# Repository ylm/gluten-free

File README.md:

# Gluten-Free Project

## What is the Gluten-Free Project?

Gluten-Free Project is an open-source platform aimed at makers and musicians for real-time audio synthesis in a live setup.

It is meant to be portable, battery powered, small form factor self-contained and highly reconfigurable synthesizer.

GF-MINUS1 is the first iteration of the core of Gluten-Free. It features a low-power FPGA as its fully customizable soundchip and a SAME53 for high-speed communication. The soundchip provides two independant stereo outputs as well as a PMOD expansion interface. It is a bare-bone version designed to interface with expansion boards.

## Why Gluten-Free?

Gluten-Free was initiated to push the boundaries of what was available to makers with a music inclination.

It is also a platform meant to learn about digital design on a platform including an FPGA connected through an high-speed interface to a microcontroller.

## What can I do with Gluten-Free?

### GF-MINUS1

GF-MINUS1 is still in active development. As development progresses, the list of its capabilities is going to be expanded.

## Where is Gluten-Free Project going?

Gluten-Free is looking to expend the DIY synthesizer community and its userbase. The goal is to provide a powerful platform able to provide the computing power required for modern synthesizers for makers to focus on their desired implementation.

## How to get involved?

We are most on our [Discord channel](https://discord.gg/bngMxeF9Fw), so feel free to join and ask questions, offer suggestions, etc. The development is mostly done live on [gatin00b's Twitch channel](www.twitch.tv/gatin00b) is also a great place for discussion.

## Who's working on Gluten-Free?

* [@gatin00b](www.twitter.com/gatin00b) started the initial design. 
* [@overtinkerer]() provided help with documentation and support of the Gluten-Free platform.
* [@vmttmv]() provided guidance on microcontroller selection.
* [@BlindVia](https://www.twitch.tv/BlindVia) provided guidance for manufacturing and a full review of Gluten-Free

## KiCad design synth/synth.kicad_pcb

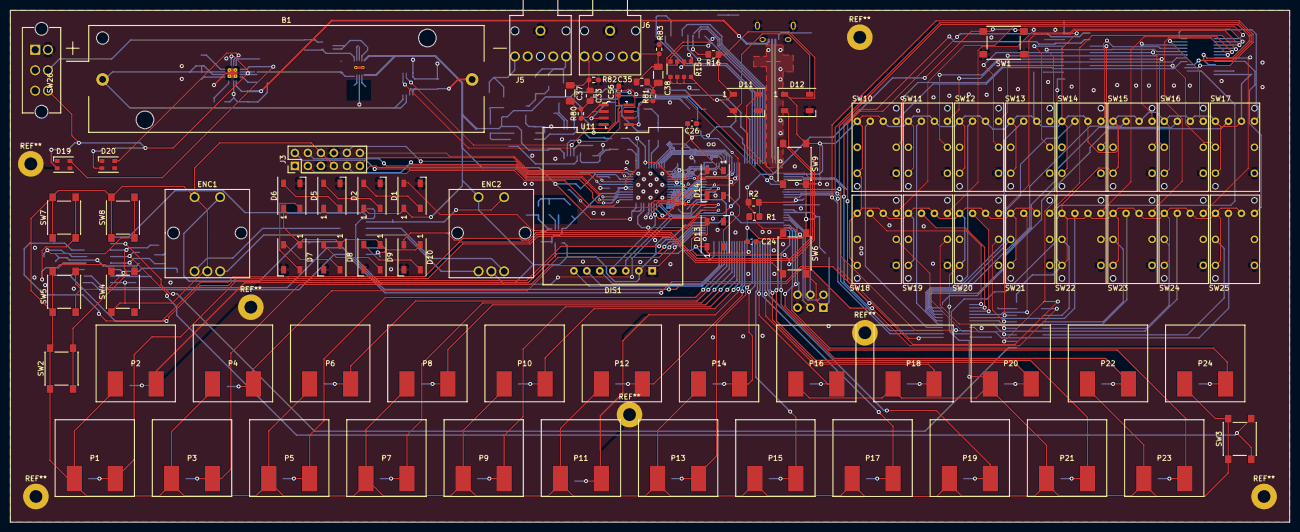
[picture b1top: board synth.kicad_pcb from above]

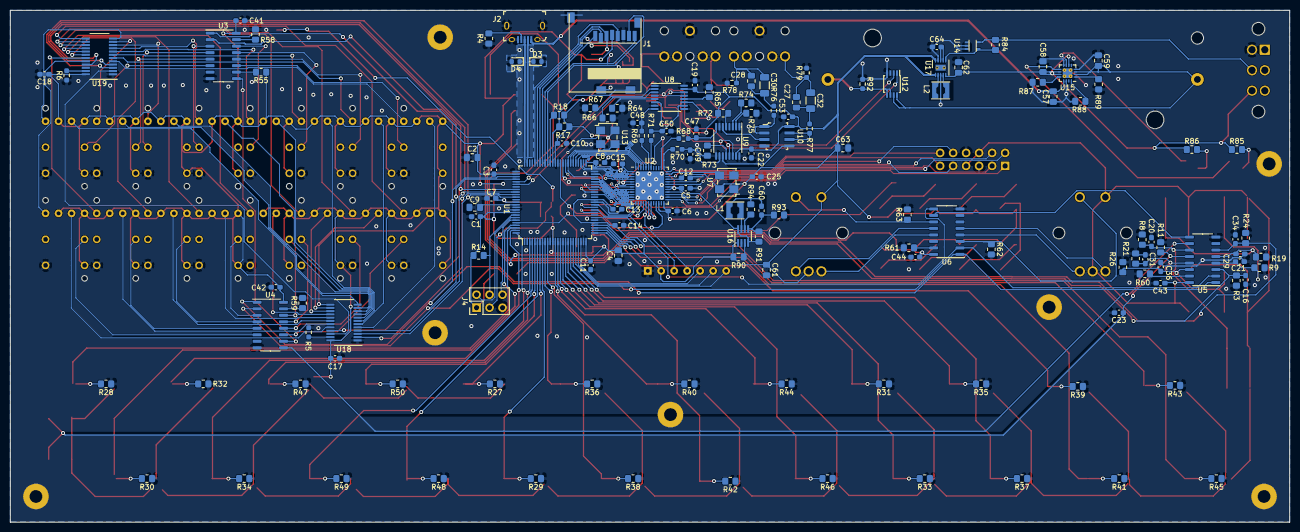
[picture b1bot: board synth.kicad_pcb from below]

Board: 2 copper layers, 250.0 x 100.0 mm, 233 parts (146 on the bottom side), 225 nets.

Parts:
B1: 186501_1043P; BatteryHolder_Keystone_1043_1x18650
C1, C3, C5, C6, C7, C8, C10, C11, C12, C13, C14, C15, C16, C17, C18, C19, C20, C21, C22, C23, C24, C25, C26, C29, C31, C34, C36, C41, C42, C43, C44, C53, C56, C64: 0.1uF_10V_0603; C_0603_1608Metric_Pad1.08x0.95mm_HandSolder
C2, C4, C63: 10uF_10V_0805; C_0805_2012Metric_Pad1.18x1.45mm_HandSolder
C9, C58, C59, C61, C62: 4.7uF_10V_0805; C_0805_2012Metric_Pad1.18x1.45mm_HandSolder
C27, C28, C33, C35: C_47uF_0805; C_0805_2012Metric_Pad1.18x1.45mm_HandSolder
C30, C32, C37, C38: C_220uF_1206; C_1206_3216Metric_Pad1.33x1.80mm_HandSolder
C47, C48, C49, C50: C_150pF_10V_0603; C_0603_1608Metric_Pad1.08x0.95mm_HandSolder
C57: 1.0uF_10V_0805; C_0805_2012Metric_Pad1.18x1.45mm_HandSolder
C60: 27pF_10V_0603; C_0603_1608Metric_Pad1.08x0.95mm_HandSolder
D1, D2, D5, D6, D7, D8, D9, D10, D11, D12, D13, D14: WS2812B; LED_WS2812B_PLCC4_5.0x5.0mm_P3.2mm
D3, D4: PGB1010603; D_0603_1608Metric
D19, D20: LED; LED_Cree-PLCC4_3.2x2.8mm_CCW
DIS1: SSD1306
ENC1, ENC2: rot_encoder_switch; PEC12R-4xxxF-Sxx
J1: MEM2061-01-188-00-A
J2: 10118194-0001LF; USB_Micro_B_Female_10118194-0001LF
J3: PMOD_conn; PinHeader_2x06_P2.54mm_Vertical
J4: debug_conn; PinHeader_2x03_P2.54mm_Vertical
J5, J6: AudioJack3_SwitchTR; STX-3120-5B-577C
L1: 22uH; LPS3015
L2: Inductance; LPS3015
P1, P2, P3, P4, P5, P6, P7, P8, P9, P10, P11, P12, P13, P14, P15, P16, P17, P18, P19, P20, P21, P22, P23, P24: keypad; DIY_KEYPAD
R1, R16, R17, R18, R89: 10kR; R_0805_2012Metric_Pad1.20x1.40mm_HandSolder
R2, R14, R27, R28, R29, R30, R31, R32, R33, R34, R35, R36, R37, R38, R39, R40, R41, R42, R43, R44, R45, R46, R47, R48, R49, R50, R85, R86: 1kR; R_0805_2012Metric_Pad1.20x1.40mm_HandSolder
R3, R4, R8, R9, R11, R19, R21, R24, R26, R55, R58, R59, R60, R61, R62, R63, R64, R65, R66, R67, R72, R73, R74, R75, R84, R90, R93, R94: 360kR; R_0805_2012Metric_Pad1.20x1.40mm_HandSolder
R5, R6: R_4k3R_0603; R_0603_1608Metric_Pad0.98x0.95mm_HandSolder
R15: 100kR_4xArray; R_Array_Convex_4x1206
R68, R69, R70, R71: R_36kR_0603; R_0603_1608Metric_Pad0.98x0.95mm_HandSolder
R76, R77, R80, R81: R_16R_0603; R_0603_1608Metric_Pad0.98x0.95mm_HandSolder
R78, R79, R82, R83: R_50kR_0603; R_0603_1608Metric_Pad0.98x0.95mm_HandSolder
R87: 3kR; R_0805_2012Metric_Pad1.20x1.40mm_HandSolder
R88: 1.8kR; R_0805_2012Metric_Pad1.20x1.40mm_HandSolder
R91: 180kR; R_0805_2012Metric_Pad1.20x1.40mm_HandSolder
R92: R_20mR_0603; R_0603_1608Metric_Pad0.98x0.95mm_HandSolder
SW1, SW2, SW3, SW4, SW5, SW6, SW7, SW8, SW9: SW_Push; SW_Push_1P1T_NO_6x6mm_H9.5mm
SW10, SW11, SW12, SW13, SW14, SW15, SW16, SW17, SW18, SW19, SW20, SW21, SW22, SW23, SW24, SW25: PB86-A2
SW26: SW_DPDT_x2_MFS201N−16−Z; SW_E-Switch_MFS201N−16−Z_DPDT
U1: ATSAME53N19A; TQFP-100_14x14mm_P0.5mm
U2: DRA818_iCE40-UP5K-SG48; QFN-48-1EP_7x7mm_P0.5mm_EP5.6x5.6mm
U3, U4, U5, U6: 74HC165; SO-16_3.9x9.9mm_P1.27mm
U7, U13: DSC6003JI2A; Oscillator_SMD_TXC_7C-4Pin_5.0x3.2mm_HandSoldering
U8, U9: DS1881; TSSOP-16_4.4x5mm_P0.65mm
U10, U11: AD8531; SOIC-8_W3.9mm
U12: DS2745; TSSOP-8_3x3mm_P0.65mm
U14: LMS33460; SC-70-5
U15: BQ24074; QFN-16-1EP_3x3mm_P0.5mm_EP1.9x1.9mm_ThermalVias
U16: TPS62120DCNR; SOT-23-8_Handsoldering
U17: TPS63031; VSON-10-1EP_3x3mm_P0.5mm_EP1.2x2mm_ThermalVias
U18, U19: STP16CPC26PTR; QSOP-24_3.9x8.7mm_P0.635mm

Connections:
+1V2: C5.2, C60.1, L1.2, R91.1, R94.2, U2.5, U2.29, U2.30, U16.4, U16.8
+3V3: C1.2, C2.2, C3.2, C4.2, C6.1, C8.2, C10.2, C11.2, C12.2, C13.2, C14.2, C15.1, C17.1, C18.1, C19.1, C22.1, C24.2, C25.2, C26.2, C41.2, C42.2, C43.2, C44.2, C53.1, C56.1, C61.1, C63.1, D1.1, D2.1, D5.1, D6.1, D7.1, D8.1, D9.1, D10.1, D11.1, D12.1, D13.1, D14.1, DIS1.2, ENC1.1, ENC1.4, ENC2.1, ENC2.4, J1.4, J3.6, J3.7, J4.1, P1.1, P2.1, P3.1, P4.1, P5.1, P6.1, P7.1, P8.1, P9.1, P10.1, P11.1, P12.1, P13.1, P14.1, P15.1, P16.1, P17.1, P18.1, P19.1, P20.1, P21.1, P22.1, P23.1, P24.1, R1.1, R14.1, R15.5, R15.6, R15.7, R15.8, R16.1, R17.1, R18.1, R55.2, R72.2, R90.2, SW2.1, SW3.1, SW4.1, SW5.1, SW6.1, SW7.1, SW8.1, SW9.1, SW10.2, SW10.4, SW10.6, SW11.2, SW11.4, SW11.6, SW12.2, SW12.4, SW12.6, SW13.2, SW13.4, SW13.6, SW14.2, SW14.4, SW14.6, SW15.2, SW15.4, SW15.6, SW16.2, SW16.4, SW16.6, SW17.2, SW17.4, SW17.6, SW18.2, SW18.4, SW18.6, SW19.2, SW19.4, SW19.6, SW20.2, SW20.4, SW20.6, SW21.2, SW21.4, SW21.6, SW22.2, SW22.4, SW22.6, SW23.2, SW23.4, SW23.6, SW24.2, SW24.4, SW24.6, SW25.2, SW25.4, SW25.6, U1.12, U1.25, U1.30, U1.39, U1.51, U1.63, U1.77, U1.91, U1.92, U2.1, U2.22, U2.24, U2.33, U3.16, U4.16, U5.16, U6.16, U7.4, U8.15, U9.15, U10.8, U11.8, U13.4, U16.1, U17.1, U17.10, U18.24, U19.24
+BATT: B1.1, C59.1, U12.7, U12.8, U15.2, U15.3
-BATT: B1.2, R92.1, U12.5, U12.6
/ADC0IN[0]: P16.2, R27.2, U1.7
/ADC0IN[1]: P15.2, R29.2, U1.8
/ADC0IN[2]: P10.2, R44.2, U1.15
/ADC0IN[3]: P9.2, R46.2, U1.16
/ADC0IN[4]: P8.2, R31.2, U1.17
/ADC0IN[5]: P7.2, R33.2, U1.18
/ADC0IN[6]: P6.2, R35.2, U1.19
/ADC0IN[7]: P5.2, R37.2, U1.20
/ADC0IN[8]: P4.2, R39.2, U1.26
/ADC0IN[9]: P3.2, R41.2, U1.27
/ADC0IN[10]: P2.2, R43.2, U1.28
/ADC0IN[11]: P1.2, R45.2, U1.29
/ADC0IN[12]: P24.2, R28.2, U1.97
/ADC0IN[13]: P23.2, R30.2, U1.98
/ADC0IN[14]: P22.2, R32.2, U1.99
/ADC0IN[15]: P21.2, R34.2, U1.100
/ADC1IN[4]: P17.2, R48.2, U1.6
/ADC1IN[5]: P18.2, R50.2, U1.5
/ADC1IN[6]: P14.2, R36.2, U1.9
/ADC1IN[7]: P13.2, R38.2, U1.10
/ADC1IN[8]: P12.2, R40.2, U1.13
/ADC1IN[9]: P11.2, R42.2, U1.14
/ADC1IN[10]: P20.2, R47.2, U1.3
/ADC1IN[11]: P19.2, R49.2, U1.4
/Analog Output/BUF0_L: U9.11, U10.5
/Analog Output/BUF0_R: U9.6, U10.3
/Analog Output/BUF1_L: U8.11, U11.3
/Analog Output/BUF1_R: U8.6, U11.5
/Analog Output/F_PDM0_L: C49.1, R70.2, U9.10
/Analog Output/F_PDM0_R: C47.1, R68.2, U9.8
/Analog Output/F_PDM1_L: C50.1, R71.2, U8.10
/Analog Output/F_PDM1_R: C48.1, R69.2, U8.8
/CDONE: U2.7, U7.1, U13.1
/CFG_RESET_B: U1.43, U2.8
/CLK48M: U2.35, U7.3
/D+: D4.1, J2.3, U1.75
/D-: D3.1, J2.2, U1.74
/DISPLAY_CMD: DIS1.6, U1.22
/DISPLAY_CS: DIS1.7, U1.21
/DISPLAY_RST: DIS1.5, U1.23
/IO/ENC1_A: ENC1.3, U6.5
/IO/ENC1_B: ENC1.5, U6.4
/IO/ENC2_A: ENC2.3, U6.13
/IO/ENC2_B: ENC2.5, U6.12
/IO/GLED_0: SW10.5, U18.5
/IO/GLED_1: SW11.5, U18.6
/IO/GLED_2: SW12.5, U18.7
/IO/GLED_3: SW13.5, U18.8
/IO/GLED_4: SW14.5, U18.9
/IO/GLED_5: SW15.5, U18.10
/IO/GLED_6: SW16.5, U18.11
/IO/GLED_7: SW17.5, U18.12
/IO/GLED_8: SW18.5, U18.13
/IO/GLED_9: SW19.5, U18.14
/IO/GLED_10: SW20.5, U18.15
/IO/GLED_11: SW21.5, U18.16
/IO/GLED_12: SW22.5, U18.17
/IO/GLED_13: SW23.5, U18.18
/IO/GLED_14: SW24.5, U18.19
/IO/GLED_15: SW25.5, U18.20
/IO/RLED_0: SW10.7, U19.5
/IO/RLED_1: SW11.7, U19.6
/IO/RLED_2: SW12.7, U19.7
/IO/RLED_3: SW13.7, U19.8
/IO/RLED_4: SW14.7, U19.9
/IO/RLED_5: SW15.7, U19.10
/IO/RLED_6: SW16.7, U19.11
/IO/RLED_7: SW17.7, U19.12
/IO/RLED_8: SW18.7, U19.13
/IO/RLED_9: SW19.7, U19.14
/IO/RLED_10: SW20.7, U19.15
/IO/RLED_11: SW21.7, U19.16
/IO/RLED_12: SW22.7, U19.17
/IO/RLED_13: SW23.7, U19.18
/IO/RLED_14: SW24.7, U19.19
/IO/RLED_15: SW25.7, U19.20
/IO/SW_BTN0: SW10.1, U3.11
/IO/SW_BTN1: SW11.1, U3.12
/IO/SW_BTN2: SW12.1, U3.13
/IO/SW_BTN3: SW13.1, U3.14
/IO/SW_BTN4: SW14.1, U3.3
/IO/SW_BTN5: SW15.1, U3.4
/IO/SW_BTN6: SW16.1, U3.5
/IO/SW_BTN7: SW17.1, U3.6
/IO/SW_BTN8: SW18.1, U4.11
/IO/SW_BTN9: SW19.1, U4.12
/IO/SW_BTN10: SW20.1, U4.13
/IO/SW_BTN11: SW21.1, U4.14
/IO/SW_BTN12: SW22.1, U4.3
/IO/SW_BTN13: SW23.1, U4.4
/IO/SW_BTN14: SW24.1, U4.5
/IO/SW_BTN15: SW25.1, U4.6
/IO/SW_BTN16: C20.1, R8.1, SW2.2, U5.11
/IO/SW_BTN17: C23.1, R11.1, SW3.2, U5.12
/IO/SW_BTN18: C31.1, R21.1, SW4.2, U5.13
/IO/SW_BTN19: C36.1, R26.1, SW5.2, U5.14
/IO/SW_BTN20: C16.1, R3.1, SW6.2, U5.3
/IO/SW_BTN21: C21.1, R9.1, SW7.2, U5.4
/IO/SW_BTN22: C29.1, R19.1, SW8.2, U5.5
/IO/SW_BTN23: C34.1, R24.1, SW9.2, U5.6
/IO/SW_ENC1: ENC1.2, R62.1, U6.3
/IO/SW_ENC2: ENC2.2, R63.1, U6.11
/LED_DATA: D1.4, U1.96
/LED_OUT: D10.2, D11.4
/MII_GCOL: U1.61, U2.21
/MII_GCRS: U1.52, U2.2
/MII_GMDC: U1.41, U2.18
/MII_GMDIO: U1.42, U2.19
/MII_GRDV: U1.60, U2.4
/MII_GRXCK: U1.48, U1.58, U2.44, U13.3
/MII_GRXER: U1.49, U2.9
/MII_GRX[0]: U1.47, U2.10
/MII_GRX[1]: U1.46, U2.11
/MII_GRX[2]: U1.45, U2.12
/MII_GRX[3]: U1.44, U2.13
/MII_GTEN: U1.53, U2.3
/MII_GTXER: U1.59, U2.6
/MII_GTX[0]: U1.54, U2.48
/MII_GTX[1]: U1.55, U2.47
/MII_GTX[2]: U1.56, U2.46
/MII_GTX[3]: U1.57, U2.45
/OUT0_L: C27.1, C32.1, J5.5, R79.1
/OUT0_R: C28.1, C30.1, J5.2, R78.1
/OUT1_L: C33.1, C37.1, J6.5, R82.1
/OUT1_R: C35.1, C38.1, J6.2, R83.1
/PDM0_L: R70.1, U2.37
/PDM0_R: R68.1, U2.38
/PDM1_L: R71.1, U2.42
/PDM1_R: R69.1, U2.43
/PMOD[0]: J3.1, U2.25
/PMOD[1]: J3.2, U2.26
/PMOD[2]: J3.3, U2.27
/PMOD[3]: J3.4, U2.28
/PMOD[4]: J3.9, U2.31
/PMOD[5]: J3.10, U2.32
/PMOD[6]: J3.11, U2.34
/PMOD[7]: J3.12, U2.36
/PSU_EN: R84.2, SW26.5, U14.5
/Power Supply/!CHG: D19.4, U15.9
/Power Supply/!PGOOD: D20.4, U15.7
/Power Supply/BGD: R84.1, U14.4, U17.6
/SC0_SCL_PAD[1]: U1.81, U8.14, U9.14, U12.1
/SC0_SDA_PAD[0]: U1.80, U8.13, U9.13, U12.2
/SC4_CS_PAD[2]: U1.36, U2.16
/SC4_PAD[0]: DIS1.4, U1.34, U2.17
/SC4_PAD[3]: U1.37, U2.14
/SC4_SCK_PAD[1]: DIS1.3, U1.35, U2.15
/SDHC1_DAT[0]: J1.7, R15.2, U1.66
/SDHC1_DAT[1]: J1.8, R15.1, U1.67
/SDHC1_DAT[2]: J1.1, R15.4, U1.68
/SDHC1_DAT[3]: J1.2, R15.3, U1.69
/SDHC1_SDCD: J1.12, R17.2, U1.64
/SDHC1_SDCLK: J1.5, U1.71
/SDHC1_SDCMD: J1.3, R16.2, U1.70
/SDHC1_SDWP: R18.2, U1.65
/SEQ_CLK: U1.86, U18.3, U19.3
/SEQ_DATA: U1.85, U18.2
/SEQ_LE: U1.84, U18.4, U19.4
/SEQ_OE: U1.83, U18.21, U19.21
/SWCLK: J4.4, R14.2, U1.93
/SWDIO: J4.2, U1.94
/SWO: J4.6, U1.95
/SW_CLK: U1.79, U3.2, U4.2, U5.2, U6.2
/SW_DATA: U1.32, U6.9
/SW_LOAD: U1.78, U3.1, U4.1, U5.1, U6.1
/Vout: C58.2, C62.1, R85.1, R86.1, SW26.6, U15.6, U15.10, U15.11, U17.5
/dbg_rst: J4.3, R2.1, SW1.2
/mcu_core: C9.1, U1.89
GND: C1.1, C2.1, C3.1, C4.1, C5.1, C6.2, C7.2, C8.1, C9.2, C10.1, C11.1, C12.1, C13.1, C14.1, C15.2, C16.2, C17.2, C18.2, C19.2, C20.2, C21.2, C22.2, C23.2, C24.1, C25.1, C26.1, C29.2, C31.2, C34.2, C36.2, C41.1, C42.1, C43.1, C44.1, C47.2, C48.2, C49.2, C50.2, C53.2, C56.2, C57.2, C58.1, C59.2, C61.2, C62.2, C63.2, C64.2, D1.3, D2.3, D3.2, D4.2, D5.3, D6.3, D7.3, D8.3, D9.3, D10.3, D11.3, D12.3, D13.3, D14.3, DIS1.1, J1.6, J1.9, J1.13, J2.5, J2.SH, J3.5, J3.8, J4.5, J5.1, J6.1, R3.2, R4.2, R5.1, R6.1, R8.2, R9.2, R11.2, R19.2, R21.2, R24.2, R26.2, R27.1, R28.1, R29.1, R30.1, R31.1, R32.1, R33.1, R34.1, R35.1, R36.1, R37.1, R38.1, R39.1, R40.1, R41.1, R42.1, R43.1, R44.1, R45.1, R46.1, R47.1, R48.1, R49.1, R50.1, R58.2, R59.2, R60.2, R61.2, R62.2, R63.2, R64.2, R65.2, R66.2, R67.2, R73.2, R74.2, R75.2, R78.2, R79.2, R82.2, R83.2, R87.1, R88.1, R89.2, R92.2, R93.1, SW1.1, SW10.3, SW11.3, SW12.3, SW13.3, SW14.3, SW15.3, SW16.3, SW17.3, SW18.3, SW19.3, SW20.3, SW21.3, SW22.3, SW23.3, SW24.3, SW25.3, SW26.4, U1.11, U1.24, U1.31, U1.38, U1.50, U1.62, U1.76, U1.90, U2.49, U3.8, U4.8, U5.8, U6.8, U7.2, U8.1, U8.7, U8.9, U8.16, U9.1, U9.7, U9.9, U9.16, U10.4, U11.4, U12.4, U13.2, U14.2, U14.3, U15.4, U15.5, U15.8, U15.14, U15.17, U16.2, U17.3, U17.9, U18.1, U19.1
unnamed: C7.1, R1.2, R2.2, U1.88
unnamed: C27.2, C32.2, R77.2
unnamed: C28.2, C30.2, R76.2
unnamed: C33.2, C37.2, R80.2
unnamed: C35.2, C38.2, R81.2
unnamed: C60.2, R91.2, R93.2, U16.5
unnamed: C64.1, U17.7, U17.8
unnamed: D1.2, D2.4
unnamed: D2.2, D5.4
unnamed: D5.2, D6.4
unnamed: D6.2, D7.4
unnamed: D7.2, D8.4
unnamed: D8.2, D9.4
unnamed: D9.2, D10.4
unnamed: D11.2, D12.4
unnamed: D12.2, D13.4
unnamed: D13.2, D14.4
unnamed: D19.2, R85.2
unnamed: D20.2, R86.2
unnamed: J2.4, R4.1
unnamed: L1.1, U16.7
unnamed: L2.1, U17.4
unnamed: L2.2, U17.2
unnamed: R5.2, U18.23
unnamed: R6.2, U19.23
unnamed: R55.1, U3.10
unnamed: R58.1, U3.15
unnamed: R59.1, U4.15
unnamed: R60.1, U5.15
unnamed: R61.1, U6.15
unnamed: R64.1, U8.5
unnamed: R65.1, U8.12
unnamed: R66.1, U8.3
unnamed: R67.1, U8.2
unnamed: R72.1, U9.5
unnamed: R73.1, U9.12
unnamed: R74.1, U9.3
unnamed: R75.1, U9.2
unnamed: R76.1, U10.1, U10.2
unnamed: R77.1, U10.6, U10.7
unnamed: R80.1, U11.1, U11.2
unnamed: R81.1, U11.6, U11.7
unnamed: R87.2, U15.12
unnamed: R88.2, U15.16
unnamed: R89.1, U15.1
unnamed: R90.1, U16.3
unnamed: R94.1, U16.6
unnamed: U3.9, U4.10
unnamed: U4.9, U5.10
unnamed: U5.9, U6.10
unnamed: U18.22, U19.2
VBUS: C57.1, J2.1, U15.13

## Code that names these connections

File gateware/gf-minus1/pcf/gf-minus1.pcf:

set_io pmod[0] 25
set_io pmod[1] 26
set_io pmod[2] 27
set_io pmod[3] 28
set_io pmod[4] 31
set_io pmod[5] 32
set_io pmod[6] 34
set_io pmod[7] 36
set_io clk48m 35

set_io mii_grxck 44
set_io mii_grx[0] 10
set_io mii_grx[1] 11
set_io mii_grx[2] 12
set_io mii_grx[3] 13
set_io mii_grdv 6
set_io mii_grxer 21
set_io mii_gcrs 20

set_io mii_gtxck 9
set_io mii_gtx[0] 3
set_io mii_gtx[1] 2
set_io mii_gtx[2] 48
set_io mii_gtx[3] 47
set_io mii_gten 4
set_io mii_gtxer 46
set_io mii_gcol 45

set_io mii_gmdio 18
set_io mii_gmdc 19

set_io pdm0_l 38
set_io pdm0_r 37
set_io pdm1_l 43
set_io pdm1_r 42

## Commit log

2021-04-21 WIP: More part selection
2021-04-22 WIP: Part selection
2021-04-22 Create streamlog
    How about a simple log of what was done during the stream?
2021-04-23 Update streamlog
2021-04-24 Project update from 20210423 stream.
2021-04-27 Design progress of stream 20210426
2021-04-27 Progress from 20210427 stream. Thanks alelondon for the help and MitsyMae for stopping by!
2021-04-28 Progress made on stream 20210428
2021-04-29 Progress of 20210429 stream.
2021-05-04 Stream 20210503 progress
2021-05-04 Stream 20210504 progress
2021-05-05 Stream 20210505 progress
2021-05-06 Stream 20210506 progress.
2021-05-08 Stream 20210507 progress
2021-05-15 Stream progress
2021-05-17 Dummy
2021-05-18 Stream 20210517 progress
2021-05-21 Progress with footprints
2021-05-25 Design checkpoint of 20210525
2021-05-29 Stream 20210528 progress checkpoint.
2021-06-05 Project checkpoint on 20210604
2021-06-08 Design checkpoint for 20210607
2021-06-09 Design checkpoint at 20210609
2021-06-10 Design checkpoint for 20210610
2021-06-17 Design checkpoint at 20210617
2021-06-22 Design checkpoint at 20210621
2021-06-22 Design checkpoint on 20210622
2021-06-24 Design checkpoint at 20210624
2021-06-29 Design checkpoint @20210628
2021-07-01 Design checkpoint at 20210701
2021-07-03 Design checkpoint at 20210702
2021-07-06 Design checkpoint on 20210706
2021-07-07 Design checkpoint of 20210707
2021-07-13 Design checkpoint at 20210712
2021-07-13 Design checkpoint on 20210713
2021-07-15 Design checkpoint for 20210715
2021-07-17 Design checkpoint on 20210716
2021-07-20 Design checkpoint on 20210719
2021-07-21 Design checkpoint on 20210721
2021-07-27 Design checkpoint on 20210726
2021-07-27 Design checkpoint on 20210727
2021-07-29 Update and fix power switch and battery holder footprints
2021-08-04 Design checkpoint on 20210804
2021-08-04 Tweak routing
2021-08-07 Small changes to the PCB
2021-08-07 Add Mountinghole footprint
2021-08-25 Initial commit of GF-MINUS1 design
2021-09-14 GF-MINUS1 progress
2021-09-23 Checkpoint before audio re-layout
2021-09-28 Review ready version of GF-MINUS1
2021-10-12 Board review fixes
2021-10-15 Most finish touch
2021-10-16 Update README.md for proper documentation
2021-10-16 Fix links in README.md file
2021-10-16 Update Discord invite link
2021-10-19 Add generated outputs of gf-minus1 revA
2021-10-19 Reorganizing project file structure
2021-10-19 Move symbols and footpriint libraries in their own directory
2021-10-19 Fix typo
2021-10-19 Scale PB86 courtyard to documented part's size
2021-11-16 Initial commit of gf-minus1 gateware
2021-12-09 Connect PDM to ethernet data stream
2021-12-14 Add testbench scripts for first order delta-sigma DAC
2021-12-21 Integrate Apicula Delta-Sigma modulator
2022-01-04 Add test fixture to properly characterize the DAC
2022-01-11 WIP: First iteration of multiplierless interpolator
    Multiply register is improperly handled
2022-01-12 WIP: interpolator sorta working, but overflows
2022-01-15 Functional 10x interpolator (still too much harmonics)
2022-01-25 Interpolate signal from 48kHz to 48MHz
2022-02-08 Add and fix WIP
2022-02-22 Add support for HX8K breakout board
2022-03-23 Add I2S receiver w/ functional testbench
2022-03-23 Create TODO list
